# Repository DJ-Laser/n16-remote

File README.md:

# N16 Remote
A small 10-key macropad for controlling my n16 wm setup

Features arrow keys, size up and down keys, three misc function keys, and a "capslock esque" key to modify their behavior (eg arrows: navigate -> move window)
Each switch is mounted north-facing for per-key north facing rgb, which can be used to show the leyer/modfier state or just to be rgb and flashy

Cad: [onshape document](https://cad.onshape.com/documents/fadd4340fdcb2f9894b9d56e/w/4e9dbccf657b58782bca758e/e/9d8bbcccd8311ae2ad41f28e)

Bom: [./bom.md](./bom.md)

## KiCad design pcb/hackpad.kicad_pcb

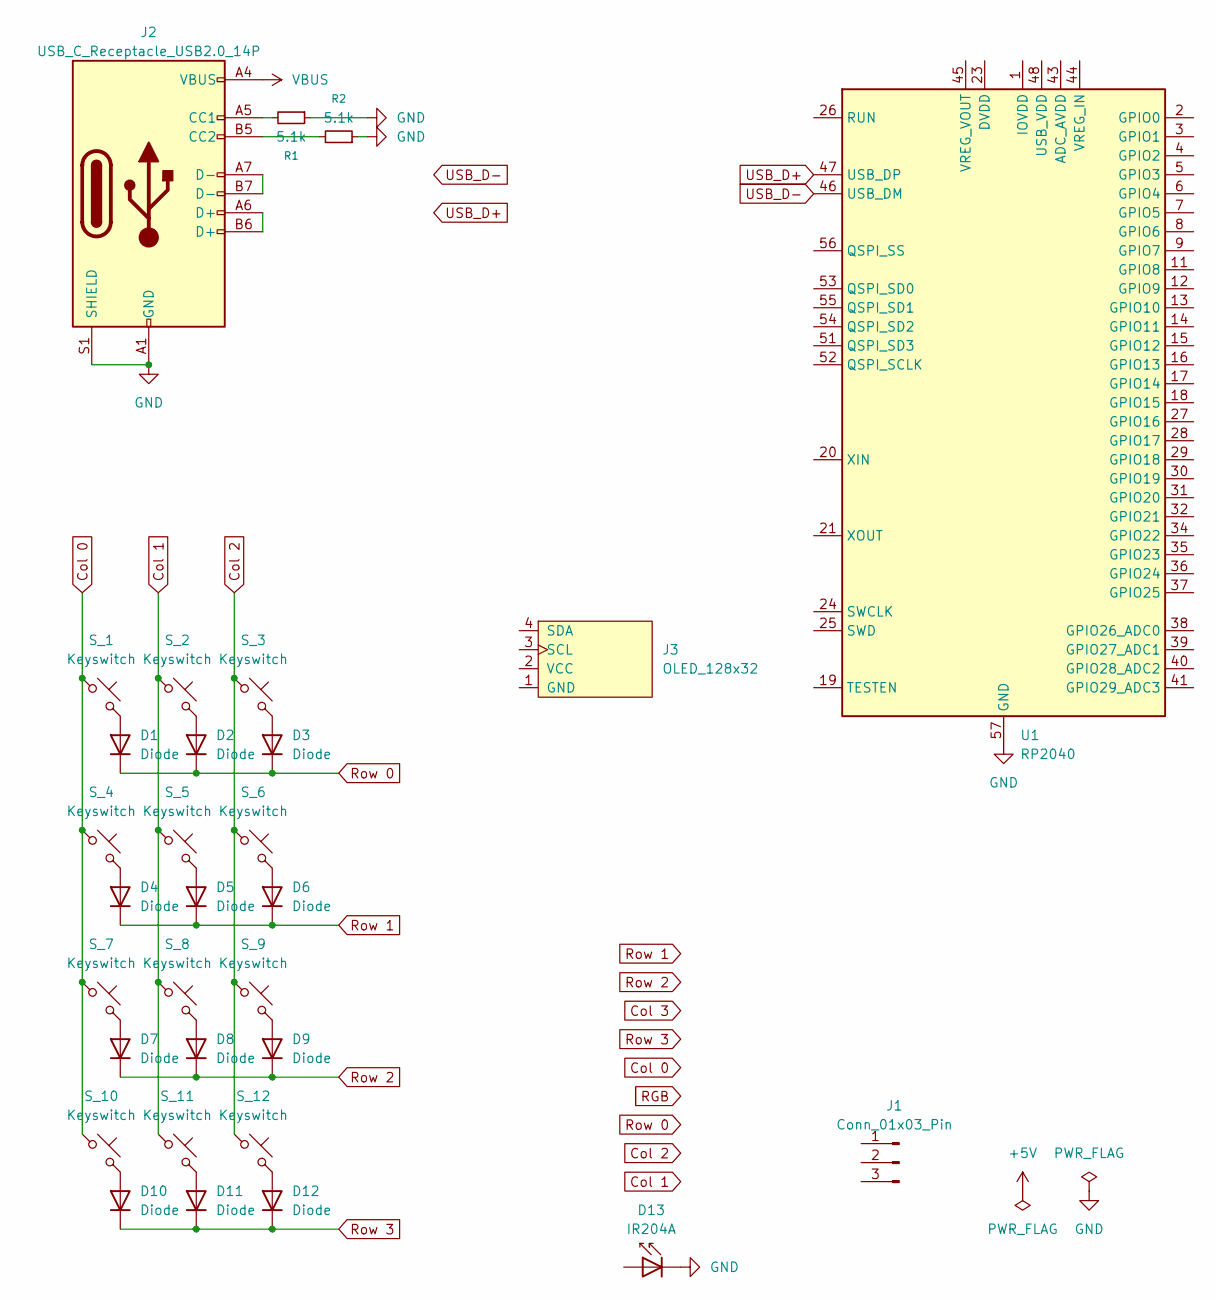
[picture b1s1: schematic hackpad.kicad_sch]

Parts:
D1, D2, D3, D4, D5, D6, D7, D8, D9, D10, D11, D12: Diode; D_DO-35_SOD27_P7.62mm_Horizontal
D13: IR204A; LED_D3.0mm_IRBlack
J1: Conn_01x03_Pin; PinHeader_1x03_P1.00mm_Horizontal
J2: USB_C_Receptacle_USB2.0_14P
J3: OLED_128x32
R1, R2: 5.1k
S_1, S_2, S_3, S_4, S_5, S_6, S_7, S_8, S_9, S_10, S_11, S_12: Keyswitch; Choc_V2_1.00u
U1: RP2040; QFN-56-1EP_7x7mm_P0.4mm_EP3.2x3.2mm

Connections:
Col 0: S_1.1, S_4.1, S_7.1, S_10.1
Col 1: S_2.1, S_5.1, S_8.1, S_11.1
Col 2: S_3.1, S_6.1, S_9.1, S_12.1
GND: D13.1 (K), J2.A1 (GND), J2.A12 (GND), J2.B1 (GND), J2.B12 (GND), J2.S1 (SHIELD), R1.1, R2.1, U1.57 (GND)
unnamed: D1.2 (A), S_1.2
unnamed: D2.2 (A), S_2.2
unnamed: D3.2 (A), S_3.2
unnamed: D4.2 (A), S_4.2
unnamed: D5.2 (A), S_5.2
unnamed: D6.2 (A), S_6.2
unnamed: D7.2 (A), S_7.2
unnamed: D8.2 (A), S_8.2
unnamed: D9.2 (A), S_9.2
unnamed: D10.2 (A), S_10.2
unnamed: D11.2 (A), S_11.2
unnamed: D12.2 (A), S_12.2
unnamed: J2.A4 (VBUS), J2.A9 (VBUS), J2.B4 (VBUS), J2.B9 (VBUS)
unnamed: J2.A5 (CC1), R1.2
unnamed: J2.A6 (D+), J2.B6 (D+)
unnamed: J2.A7 (D-), J2.B7 (D-)
unnamed: J2.B5 (CC2), R2.2
unnamed: U1.23 (DVDD), U1.50 (DVDD)
unnamed: U1.1 (IOVDD), U1.10 (IOVDD), U1.22 (IOVDD), U1.33 (IOVDD), U1.42 (IOVDD), U1.49 (IOVDD)
Row 0: D1.1 (K), D2.1 (K), D3.1 (K)
Row 1: D4.1 (K), D5.1 (K), D6.1 (K)
Row 2: D7.1 (K), D8.1 (K), D9.1 (K)
Row 3: D10.1 (K), D11.1 (K), D12.1 (K)
USB_D+: U1.47 (USB_DP)
USB_D-: U1.46 (USB_DM)

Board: 2 copper layers, 28 parts (1 on the bottom side), 22 nets, no tracks yet.

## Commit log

2025-02-06 add pcb
2025-02-06 add text and qr code silkscreen
2025-02-07 increase text thicknesss (drc is mad at me still tho)
2025-02-08 i used the wrong data sheet to edit the footprint, changed the pcb to actually work :(
2025-02-08 fix drc errors (by lowering clearance)
2025-02-09 regenerate gerber
2025-02-09 add direnv
2025-02-09 update flake
2025-02-09 init led blink example
2025-02-09 switch to embassy
2025-02-10 the leds on the xiao are linked to gnd
2025-02-10 add keyboard and debouncer traits
2025-02-11 fix rust source path
2025-02-11 add basic debouncer
2025-02-11 use one config type only
2025-02-11 add runner logic
2025-02-11 use update callback instead of direct access
2025-02-11 add maytrix scanning impl (inspired by rmk firware)
2025-02-12 now you can actually instantiiate these structs!
2025-02-14 make erc happy
2025-02-16 add holes for mounting the case to the pcb
2025-02-16 remove backup gerbers from git
2025-02-16 detriangulate step
2025-02-16 add cad models
2025-02-16 add holes to the smd debug pads
2025-02-16 moar pcb
2025-02-19 Rename BOM.md to bom.md
2025-06-27 moar gerber
2025-06-27 remove "jlcjlcjlc"
2025-06-27 implement usb device idk
2025-06-28 start journal
2025-06-28 revert xiao footprint since im gonna use smd assembly
2025-06-28 add day 1 files
